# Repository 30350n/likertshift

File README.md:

# LikertShift

The LikertShift project introduces a novel way of collecting Travel Satisfaction data while Cycling, by using a gearshift-like Device that reports to the users smartphone via BLE.

## Repository Overview

### [Hardware](hardware/)

The LikertShift hardware consists of the [CAD](hardware/cad/) files for all the 3D printed parts, as well as the design files for the LikertShift [PCB](hardware/pcb/).

The CAD files can be viewed and modified via FreeCAD and OpenSCAD, ready to print STLs with correct print orientation are available under the [`stl/`](hardware/cad/stl/) directory.

The PCB is designed using KiCad 9.0. For the first prototype we manufactured the PCBs at [Aisler](https://aisler.net/).

### [Firmware](firmware/)

The LikertShift firmware runs on the Seeed XIAO nRF52840 dev board on the LikertShift PCB. It is built with Rust and the [embassy-rs](https://github.com/embassy-rs/embassy) framework for embedded development.

### [App](app/)

The LikertShift App provides different methods for recording Travel Satisfaction while Cycling (or any other data, that can be represented on a Likert Scale).

#### Supported Recording Methods

- LikertShift Device
- Synchronized Audio Recording
- Retrospective Manual Mapping

It supports storing pre-defined routes, but can all also be used for free-roaming.

It is designed to be easily customizable, so you can adjust it to your needs to conduct you own Field Studies.

#### Data-Privacy

The App stores all the recorded data locally.

The `Export Data & Reset` option in the `Settings` tab can be used to export all the recorded data to a `.zip` archive and subsequently delete it from the local App storage.

*Note: Usage of the [MapTiler API](app/lib/api-keys/README.md#maptilerdart) allows [MapTiler AG](https://www.maptiler.com/) to indirectly track the [users location and IP address](https://www.maptiler.com/privacy-policy/).*

## Licenses

- The code included in this project is licensed under the [MIT](app/LICENSE) license.

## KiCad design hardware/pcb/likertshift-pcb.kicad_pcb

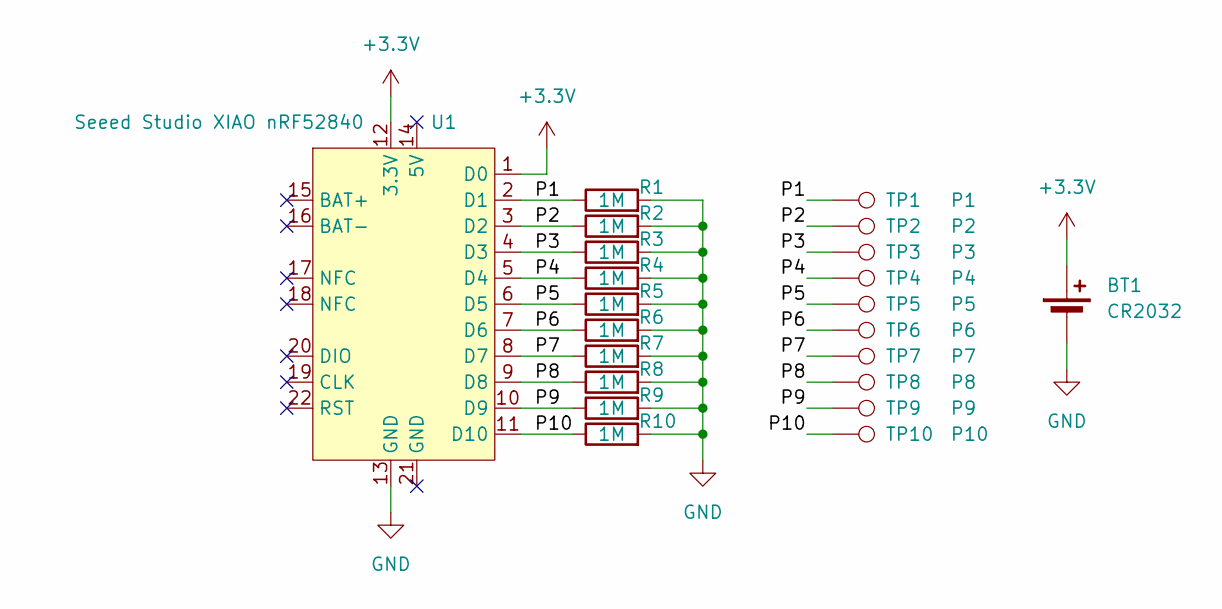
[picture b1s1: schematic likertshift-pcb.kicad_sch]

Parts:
BT1: CR2032; BatteryHolder_Keystone_1058_1x2032
R1, R2, R3, R4, R5, R6, R7, R8, R9, R10: 1M; R_0603_1608Metric_Pad0.98x0.95mm_HandSolder
TP1: P1; TestPoint_Pad_D2.0mm
TP2: P2; TestPoint_Pad_D2.0mm
TP3: P3; TestPoint_Pad_D2.0mm
TP4: P4; TestPoint_Pad_D2.0mm
TP5: P5; TestPoint_Pad_D2.0mm
TP6: P6; TestPoint_Pad_D2.0mm
TP7: P7; TestPoint_Pad_D2.0mm
TP8: P8; TestPoint_Pad_D2.0mm
TP9: P9; TestPoint_Pad_D2.0mm
TP10: P10; TestPoint_Pad_D2.0mm
U1: Seeed Studio XIAO nRF52840; XIAO-nRF52840-SMD

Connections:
+3.3V: BT1.1 (+), U1.1 (D0), U1.12 (3.3V)
/P1: R1.1, TP1.1, U1.2 (D1)
/P2: R2.1, TP2.1, U1.3 (D2)
/P3: R3.1, TP3.1, U1.4 (D3)
/P4: R4.1, TP4.1, U1.5 (D4)
/P5: R5.1, TP5.1, U1.6 (D5)
/P6: R6.1, TP6.1, U1.7 (D6)
/P7: R7.1, TP7.1, U1.8 (D7)
/P8: R8.1, TP8.1, U1.9 (D8)
/P9: R9.1, TP9.1, U1.10 (D9)
/P10: R10.1, TP10.1, U1.11 (D10)
GND: BT1.2 (-), R1.2, R2.2, R3.2, R4.2, R5.2, R6.2, R7.2, R8.2, R9.2, R10.2, U1.13 (GND)

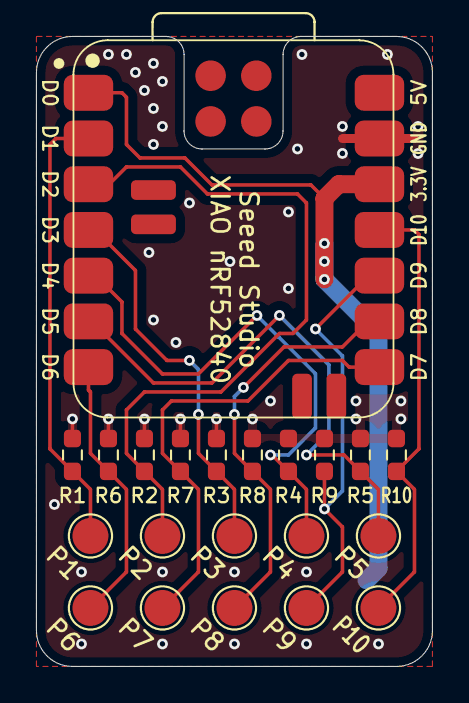
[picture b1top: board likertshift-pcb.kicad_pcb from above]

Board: 2 copper layers, 22.0 x 35.0 mm, 22 parts (1 on the bottom side), 12 nets.

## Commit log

2024-07-09 Use nrf-softdevice example as base for firmware
2024-07-09 Add shell.nix for rust firmware
2024-07-09 Initialize likertshift firmware cargo project
2024-07-09 Add vscode configurations, build tasks, softdevice s140 binary
2024-09-16 Add shell.nix for flutter app
2024-09-16 Initialize flutter app
2024-09-17 Implement basic firmware prototype
2024-09-24 Add app logo
2024-09-24 Add home page with flutter map widget using maptiler api
2024-09-24 Adjust ios project id to match android
2024-10-10 Add example routes to map
2024-10-10 Add bottom bar to home, Add settings screen, mockups for routes, devices
2024-10-10 Apply app theming to system navigation bar
2024-10-10 Add devices screen, bluetooth and location model, custom app colors
2024-10-15 Refactor bluetooth logo widget
2024-10-15 Implement connecting to bluetooth devices
2024-10-15 Add follow location functionality, location off warning, Refactor routes
2024-10-15 Read and show values from likertshift devices
2024-10-23 Add demographics form on first startup
2024-10-23 Implement route recording
2024-10-23 Streamline recording file handling to reduce file operations
2024-10-23 Add routes screen
2024-11-01 Add audio recording
2024-11-01 Add README.md
2024-11-03 Cleanup flutter configuration files, Setup linter rules
2024-11-03 Update flutter dependencies
2024-11-03 Add app license, repository overview to readme
2024-11-04 Fix geolocator initialization
2024-11-09 Add compass to map, Implement follow rotation
2024-11-10 Load routes from json files, Add kml conversion script
2024-11-10 Add route visibility
2024-11-12 Add SeperatedListView helper class, Use it for settings
2024-11-12 Fix disposing animation controller in home widget
2024-11-12 Translate app to german
2024-11-12 Upgrade to flutter 3.26 (unstable)
2024-11-12 Add LikertScaleField for forms, Add BFI-10, TLX forms
2024-11-12 Make forms chainable, Add UEQ+ form
2024-11-12 Implement json forms, Replace demographics with json form
2024-11-12 Fix saved forms being incomplete
2024-11-12 Show bfi-10 form after demographics, tlx, ueq+ after recording
2024-11-13 Add tasks to upload firmware via DFU, refactor softdevice probe-rs task
2024-11-13 Add led blink on reset
2024-11-13 Refactor firmware pin mapping to match likertshift pcb
2024-11-13 Add button in settings to export data and reset app
2024-11-14 Use new likertshift service uuid
2024-11-14 Fix follow rotation mode
2024-11-14 Fix likertshift value display overlapping compass
2024-11-14 Fix map location off widget icon, likertshift value widget text style
2024-11-14 Add audio recording widget with dynamic amplitude display to map
2024-11-14 Fix route start points, directions
2024-11-14 Add start arrows to routes, Improve route color contrast while recording
2024-11-15 Add handedness to demographics
2024-11-15 Add weather conditions form, manual mapping screen
2024-11-15 Add reset screen to show participant id
2024-11-15 Adjust polyline thickness while recording, tweak start marker size
2024-11-15 Fix some formatting, translations
2024-11-21 Fix translations, set default language to de
2024-11-23 Add interview recording screen
2024-11-23 Fix import orders
2024-11-23 Add wakelock while recording to disable screen timeout
2024-11-23 Support LineStrings in kml route generator, Use new, shorter routes
2024-12-16 Add study data (route data)
2024-12-16 Add study data (interviews)
2024-12-17 Add filters for all routes
2024-12-17 Add plot script to test evaluation data filters
2024-12-26 Add study data (questionnaires, demographics)
2024-12-26 Add interview transcription script
2025-01-07 Add hu-berlin latex template
2025-01-07 Set thesis language to english, Enable hidelinks flag
2025-01-07 Setup title and personal data on title page
2025-01-07 Move abstract to it's own file, remove example chapters
2025-01-07 Setup thesis structure, add initial citations from proposal
2025-01-07 Capitalize "Travel Experience" in thesis title
2025-01-07 Add abstract
2025-01-07 Add references to table of contents, Remove page number from abstract
2025-01-07 Put Selbständigkeitserklärung on its own page, fix date
2025-01-07 Format latex files
2025-01-07 Add prototype design requirements to thesis
2025-01-08 Add mechanical design continuous scale discussion
2025-01-08 Add mounting, off-the-shelf vs custom built, final design sections
2025-01-14 Add motivation section
2025-01-19 Revise abstract
2025-01-19 Add route ground thruth data to plot script
2025-01-19 Finialize prototype design section, add images
2025-01-19 Add questionnaire evaluation plot script
2025-01-24 Add CSE macro
2025-01-25 Add related work
2025-01-25 Add recording methods subsection of study design
2025-01-25 Add route selection, data collection and procedure for study design
2025-01-25 Refactor plot script
2025-01-25 Refactor plot.py, Add route rating eval
2025-01-25 Only evaluate UEQ in eval_questionnaires, add separate TLX eval
2025-01-25 Rename plot.py to eval_route_ratings.py
2025-01-25 Finish thesis
2025-08-11 Cleanup unused math test functions from eval_route_ratings
2025-08-12 Fix spelling mistakes in final sections
2025-08-12 Rename main to thesis, renumber chapters, compress images
2025-08-12 Add thesis.pdf
2025-08-12 Add flake.nix for thesis
2025-08-12 Add TU Darmstadt beamer template for defense
2025-08-12 Set defense title, subtitle, name, date, etc.
2025-08-12 Move hulogo to images subfolder, Cleanup defense.tex
2025-08-13 Fix defense table of contents spacings
2025-08-13 Add motivation section to defense
2025-08-13 Add prototype design section to defense
2025-08-13 Add study design section to defense
2025-08-13 Add results and final slide to defense
2025-08-14 Add defense pdf
2025-08-14 Add pdfpc notes to defense
2025-08-14 Fix typo in prototype design chapter
2025-08-14 Add likertshift pcb KiCad files
2025-08-14 Capitalize LikertShift in README, app, firmware
2025-08-14 Add likertshift cad files
2025-08-14 Add readme to firmware

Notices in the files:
README.md:
License: MIT
